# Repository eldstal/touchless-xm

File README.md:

# Touchlæss XM

A mod for Sony WH-1000XM2 (experimental), WH-1000XM3, WH-1000XM4 and WH-1000XM5 (experimental) headphones to remove the gesture-based touch controls and add physical buttons.

- [Project Status](#Status)
- [Compatible headsets](#compatibility)
- [Modifications](#modifications-and-faq)
- [How to program your board](#how-to-program)
- [Notes on ordering PCBs](#fabrication-notes)
- [License](#license)

## Status
The project is feature-complete and the electronics are functional. I'd call it a Beta product, since I'm the only user and still tweaking the design details.

### Case
The design has been 3D-printed and test fit against an XM4 headset. The mic grill looks good but prints awful.
Could be that we need to use a metal mesh inserted during the print.

The buttons have different top surfaces, so you can feel which is which. They've also been relocated to be less likely to be accidentally actuated.

STLs will be available both with and without USB ports, with and without the Æ logo.

### PCB
v0.5c of the board has been manufactured and works great!

I've installed it in my own headset for some day-to-day testing.

### Firmware
Ready to go. USB support (only for programming) is already included in the main board. The project uses platform.io and OptiBoot to run an Arduino-based firmware.

## Compatibility
I only have a pair of XM4 to test with, so the design is made to fit them. The connector is a 24-pin, but only XM5 has a cable that wide. For other models, insert your narrower cable carefully to match the lines on the PCB.

### 🟡 Sony WH-1000XM2 (Experimental)
I've laid out the board for experimental support for the XM2. These are the most different out of the bunch, so there are caveats.

⚠️**WARNING**⚠️
The OEM cable will not work, because the XM2 has the touch board's connector at the front. You will need a slightly longer cable **with opposite side contacts**. Possibly [This Würth 687712100002](https://eu.mouser.com/ProductDetail/Wurth-Elektronik/687712100002?qs=PhR8RmCirEbjmYLiy2w9eg%3D%3D) is suitable, but too long of a cable will cause interference. If you can trim it to length, that will improve the chances of success.

There is no bespoke connector for the XM2, you need to very carefully position it in the larger connector using the lines on the PCB.

It's also necessary to modify the firmware pin map slightly, since the Y pins are in the opposite order. Use `--environment xm2` when you compile the firmware.

If you've got a pair of XM2s and want to help me tune the compatibility, let me know!

### 🟡 Sony WH-1000XM3 (Probably compatible)
The XM3 touch board and battery connector appear to be electrically identical to XM4, so the PCB should be compatible. A different case design may be needed.

Insert your cable all the way at the top of the connector (there will be two unused pins at the bottom). Follow the lines in the silkscreen for guidance.

### 🟢 Sony WH-1000XM4 (Compatible)
The project is designed for these, so these will be the ones primarily tested. The OEM touch board has a flat cable which Touchlæss is designed to reuse.

Insert your cable all the way at the top of the connector (there will be two unused pins at the bottom). Follow the lines in the silkscreen for guidance.

The battery uses a 2-pin JST ZH series connector. There is no vertical space inside the case for a matching connector on the board, so I've resorted to soldering a Y-connector onto the Touchlæss pcb. Separate from the PCB BOM, you'll need one male and one female JST ZH-2 connector and some red/black cables.

### 🟡 Sony WH-1000XM5 (Possibly compatible)
Experimental support is included in the initial board design, but I **do not** own a pair of XM5 and cannot test them. The XM5 pinout is entirely based on reverse-engineering of photos, so I may have made a mistake! The Touchless board shouldn't be able to do any damage to the headphones. If you have a pair of XM5s and would like to help me test the compatibility, feel free to reach out!

At a minimum, the XM5 OEM design doesn't include a loose cable for us to reuse. You will need a suitable flat cable, which is 24-pin FFC with 0.5mm pitch and same-side connectors. [This Würth 687624050002](https://eu.mouser.com/ProductDetail/Wurth-Elektronik/687624050002?qs=P%2FTEqz%252BQfndQFFKLalvVUA%3D%3D) should work, but may not be the proper length.

The battery connector for XM5 is also different, a 3-pin of unknown design. If you have more information about this, let me know!

### 🟡 Sony WH-1000XM6 (Not even released yet)
With any luck, the XM6 touch board will be similar to the XM5. It will be a while before I get my hands on a new high-end headset to test it, though.

If you're getting a pair of XM6 and would like to send me some nice photos of the internals, I'll be very grateful!

### 🔴 Other manufacturers/headsets
**Highly** unlikely. At the very least, you'll need to figure out the pinout for the touch sensor board. Most likely there will be other things that need tuning as well. If you want to make something like touchless for a different headset, take a look at the [technical documentation](doc/README.md) for some pointers on how Touchless works.

## Modifications and FAQ

#### Will it drain my battery?
Not really. When idle, the board draws about 0.02 mA. When you're actively pressing/holding buttons it peaks at just under 13mA. This is on the order of one LED, and only when you're actively pushing buttons.

The DC converter on the board will stop working once the battery drops below about 0.7V, which is quite a bit before the headphones actually stop working. That means the buttons won't work when your battery is very low.

#### I don't want another USB port on my headset
That's OK, it's only needed for development (reprogramming the Touchless board without disassembling the headphones). Simply snap the USB connector off from the main board (see perforations) and print yourself a case without a USB block. Set `cap_type=nousb` in `xm4-cap.scad` to get a case that's closed at the bottom.

#### I don't like how you've placed the buttons
That's no problem! Snap the button portion off of the main board (see perforations) and use the solder points on the front or back to connect your own buttons placed wherever you want them. If you're keen on PCB design, it's not that hard to redesign the PCB for button placement (or add/remove buttons as needed).

There is no need for external resistors etc, just connect a switch between one button contact and the COM and you're good to go.

#### I don't have a 3D printer
No problem! If you remove the buttons and the USB addition (see above), the touchless board should fit inside the OEM ear cup (you have to remove the original touch board first, which may be destructive). Make cuts in the case as needed to mount buttons where you want them, and wire them up to the exposed button solder points on the front or back of the PCB.

#### The case is fine, but I want to reconfigure the buttons
Easiest way to do this is in the firmware. Take a look at [buttonmap.cpp](firmware/tobo/src/buttonmap.cpp) to switch and swap however you like. You'll need the included USB port or a serial cable to program the board after you've made your modifications. Instructions are [down below](#step-2-firmware).

#### Any tips for software modifications?
The board itself works as its own development board, of sorts. If you're going to be flashing new software via USB while testing, I recommend connecting the USB V (+5v) pad to the VCC test point as shown in [this photo](doc/usbpower.png). If you also short out the "LED" solder bridge you get LED indications of which touch points are currently being "touched".

**Please disconnect the USB power jumper before installing in the headset and connecting a battery**

#### I want to design my own case
Great! You can find the dimensions of the PCB [here](doc/tobo-measurements.svg). It's all  relative to the center of the circular area, so if your CAD program supports polar coordinates you'll have an easier time of it. You may also have use for `make vrml` in the pcb directory, which creates a VRML 3D export of the PCB to use as a reference in your model.

#### I want buttons for other features
That won't be possible, sorry. Touchlæss only works by simulating touches and swipes, so it can only do what the headphones allow you to do with the touch panel.

#### The buttons are too slow!
Yes. There is a significant delay between pushing a button and the headset responding. This isn't something we can control, since Touchlæss simulates touch gestures. If a swipe takes 120ms to perform, the headset can't react sooner than that.

#### I want the buttons on the left cup
That will be an adventure. Touchlæss interfaces with the board in the right cup, so you'll need to run wires across the headband to get to the other side. Not impossible, but certainly a lot of work.

#### I want to make and sell these
That's great! I won't ask for any royalties or whatever. If you do set something up, I'm happy to include a link here so people can buy from you.

## How to program

**Note:** The VCC loop on the PCB is powered by the headset battery via a step up/step down converter configured for 3.3V. **Do not** connect an external supply to this hook while the battery is connected. The loop is only needed in order to program and test the board without a headset connected.

The board will not take power from the USB connector by default. If you want to power it via USB while programming, connect a jumper between the USB V test point and the VCC test point as illustrated [here](doc/usbpower.png). Disconnect that jumper again before connecting a battery, please.

### Step 1: Bootloader
**This only needs to be done once per board**

When you have a fresh board with a factory-stock microcontroller, you'll have to start with the bootloader. For this step you need a hardware AVR programmer, for example:

- AVRISPmk2 (tested, works)
- An Arduino ([Instructions](https://docs.arduino.cc/built-in-examples/arduino-isp/ArduinoISP/#how-to-wire-your-boards))
- A [Bus Pirate](http://www.dangerousprototypes.com/docs/Bus_Pirate_AVR_Programming)
- An [USBAsp](https://www.fischl.de/usbasp/)

...or anything else supported by avrdude or [platform.io](https://platformio.org/). Install [the platform.io tools](https://platformio.org/install/cli) and let's go!

1. Connect your programmer to MISO, MOSI, SCK, GND and RST.
2. Connect the battery or the VCC terminal

| tobo | AVRISP 10-pin |Glasgow | BP harness |
|------|---------------|--------|------------|
| MOSI | 1             | PURP   | 8 Pink     |
| VCC  | 2             | ORG    | 2 White    |
| RST  | 5             | YEL    | 6 Green    |
| SCK  | 7             | PINK   | 7 Yellow   |
| MISO | 9             | BRN    | 10 Brown   |
| GND  | 10            | B/W    | 1 Black    |

If you're using a new kind of programmer, add the needed environment to `firmware/tobo/platformio.ini` to use your programmer.

**Warning** Ensure that your new environment extends `env:tobo`, so that the frequency and fuses are programmed properly. If you do not, you may need to temporarily connect an external crystal (see PCB markings) in order to recover the board.

```
cd firmware/tobo
pio run --environment avrispv2 --target bootloader
```

If there are no errors, congratulations! Your tobo board is an Arduino! You're ready for the next step.

### Step 2: Firmware
**If you've made changes to the code and want to update your board, this step is the only one you need to repeat**

If your board has the bootloader installed, you can put your ISP programmer away and use either the on-board USB port or your own serial adapter. This can be an FTDI cable, a different USB-to-serial adapter, or an arduino board with no microcontroller.

Hook up your serial cable to the tobo:

| tobo | serial adapter |
|------|----------------|
| RX | TX |
| TX | RX |
| GND | GND |
| DTR | DTR (if your cable has it) |
| RST | RST (if using an arduino) |
| VCC  | VCC **Only if you don't have the battery plugged in**|

```
cd firmware/tobo
pio run --target upload
```

If all went well, you're ready to go!

## Fabrication Notes
I've had the board produced by PCBWay with no issues. The following facts are useful while setting up an order:

- Order a 0.6mm PCB, to maximize the clearance inside the cap
- The smallest drilled hole is just over 0.2mm
- The XM4/XM5 connector footprints have narrow spacing between pads. This is a problem for the "Matte black" solder mask, but apparently possible with green/blue/red solder mask. If you want a matte black board, you have to allow for gaps in the solder mask at these connectors, and that may lead to shorts. Go with green or blue or red.

## Cost
The total cost for production, components and assembly of 5 boards was about $280 including shipping to Europe and VAT. That works out to about $56 per board.
You can reduce the BOM cost some by removing the USB port, USB-Serial circuitry and the LEDs. You could also save a bit by not populating the test loops, but it will make it more difficult to program the board.

## License
Touchlæss XM © 2026 by Albin Eldstål-Ahrens is licensed under Creative Commons BY-SA 4.0 

This means you are free to use, modify, distribute, remix, redesign the project however you wish as long as you
1. Credit the original work where relevant
2. Release your own modified work under a similar CC license

If you want to make and sell kits of this, feel free! If you make money from my work, please consider making a donation to a charitable organization as a thank you!

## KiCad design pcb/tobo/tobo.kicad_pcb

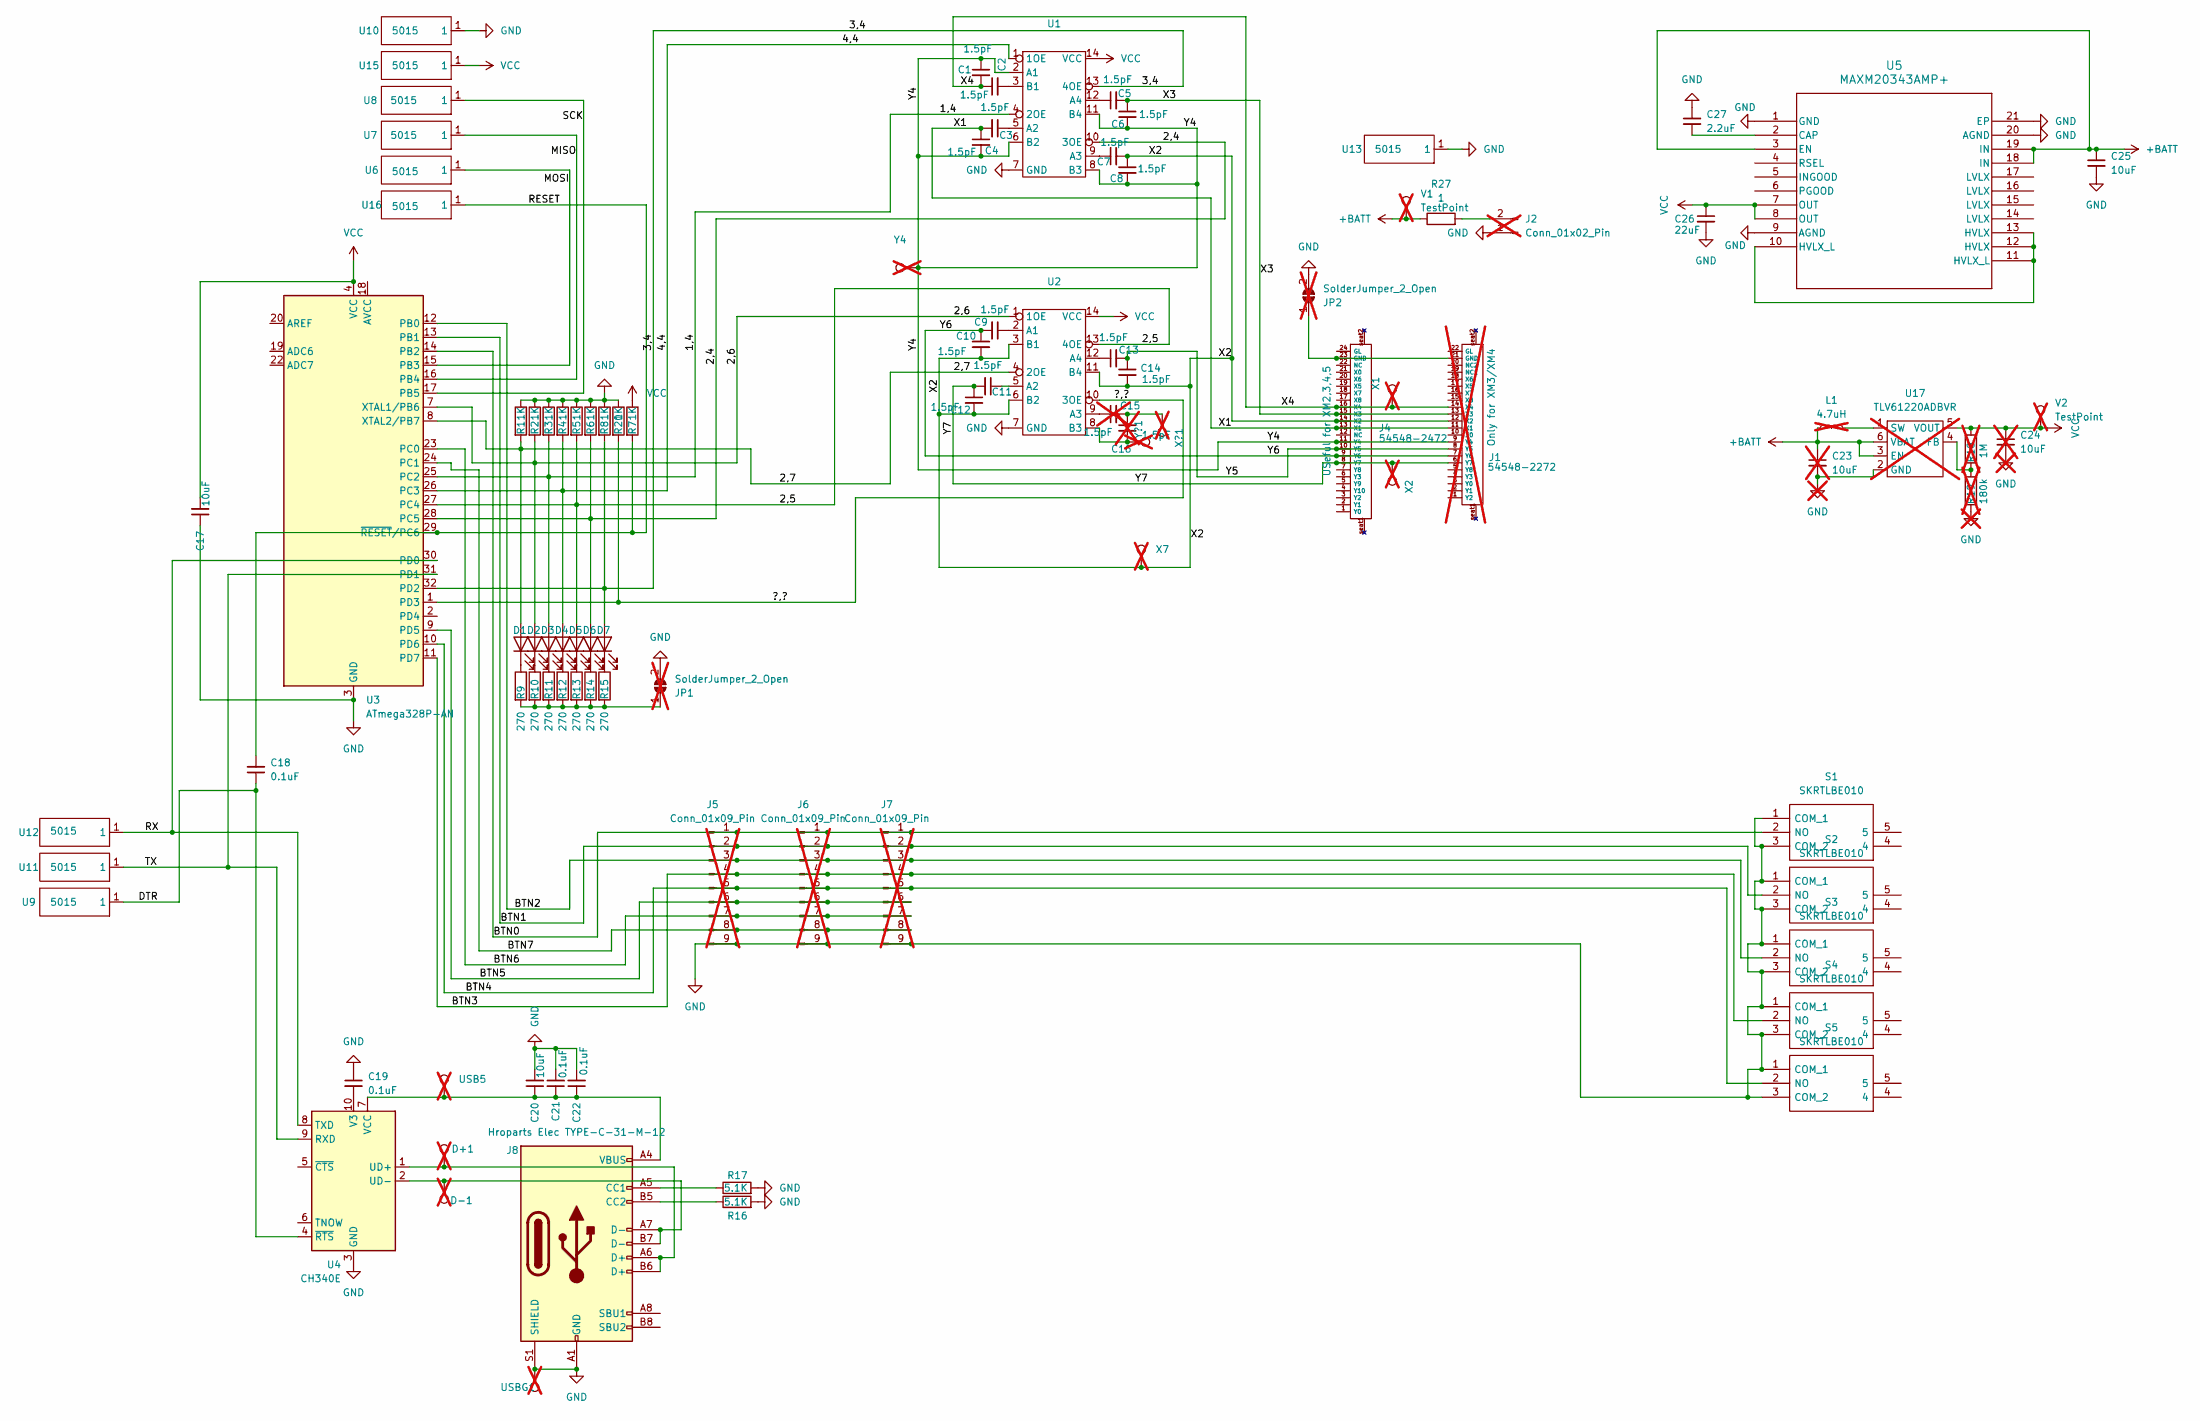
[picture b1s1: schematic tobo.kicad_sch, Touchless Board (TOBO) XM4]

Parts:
C1, C2, C3, C4, C5, C6, C7, C8, C9, C10, C11, C12, C13, C14: 1.5pF; C_0402_1005Metric; Manufacturer_Part_Number CC0402BRNPO9BN1R5; LCSC Part Number C282238
C15, C16: 1.5pF; C_Disc_D5.0mm_W2.5mm_P2.50mm; Manufacturer_Part_Number CC0402BRNPO9BN1R5; LCSC Part Number C282238; not fitted
C17, C20, C25: 10uF; C_0402_1005Metric; Manufacturer_Part_Number CL05A106MP5NUNC; LCSC Part Number C315248
C18, C19, C21, C22: 0.1uF; C_0201_0603Metric; Mouser Part Number 963-TMK063ABJ104KP-F
C23, C24: 10uF; C_0402_1005Metric; Manufacturer_Part_Number CL05A106MP5NUNC; LCSC Part Number C315248; not fitted
C26: 22uF; C_0402_1005Metric; Manufacturer_Part_Number CL05A226MQ5QUNC; LCSC Part Number C105226
C27: 2.2uF; C_0402_1005Metric; Manufacturer_Part_Number CL05A225KO5NQNC; LCSC Part Number C170151
D1, D2, D3, D4, D5, D6, D7: LED; LED_0201_0603Metric; Manufacturer_Part_Number XL-0201UYC; LCSC Part Number C5440628
D+1: TestPoint; TestPoint_Pad_D1.0mm; not fitted
D-1: TestPoint; TestPoint_Pad_D1.0mm; not fitted
J1: 54548-2272; molex-545482272; Mouser Part Number 538-54548-2272; not fitted
J2: Conn_01x02_Pin; power-cable; not fitted
J4: 54548-2472; molex-545482472; Mouser Part Number 538-54548-2472
J5: Conn_01x09_Pin; button_breakout_2.54mm; not fitted
J6, J7: Conn_01x09_Pin; button_breakout_0.5mm; not fitted
J8: Hroparts Elec TYPE-C-31-M-12; USB_C_Receptacle_HRO_TYPE-C-31-M-12; Manufacturer_Part_Number TYPE-C-31-M-12; LCSC Part Number C165948
JP1, JP2: SolderJumper_2_Open; SolderJumper-2_P1.3mm_Open_RoundedPad1.0x1.5mm; not fitted
L1: 4.7uH; L_1008_2520Metric; Mouser Part Number 571-365708M4R7T; not fitted
R1, R2, R3, R4, R5, R6, R7, R8, R20: 1K; R_0201_0603Metric; Mouser Part Number 667-ERJ-1GJJ102C
R9, R10, R11, R12, R13, R14, R15: 270; R_0201_0603Metric; Mouser Part Number 667-ERJ-1GNF2700C
R16, R17: 5.1K; R_0201_0603Metric; Mouser Part Number 667-ERA-1AEC512C
R18: 1M; R_0201_0603Metric; Mouser Part Number 667-ERJ-1GJF1004C; not fitted
R19: 180k; R_0201_0603Metric; Mouser Part Number 667-ERJ-1GJF1803C; not fitted
R27: 1; R_0805_2012Metric; Mouser Part Number 667-ERJ-6DQF1R0V
S1, S2, S3, S4, S5: SKRTLBE010; Mouser Part Number 688-SKRTLB
U1, U2: VSSOP50P400X100-14N; Mouser Part Number 757-TC7MBL3125CFKEL
U3: ATmega328P-AN; TQFP-32_7x7mm_P0.8mm; Mouser Part Number 556-ATMEGA328P-AN
U4: CH340E; MSOP-10_3x3mm_P0.5mm_narrowpads; Manufacturer_Part_Number CH340E; LCSC Part Number C99652
U5: MAXM20343AMP+; 21-100447_ADI; Manufacturer_Part_Number MAXM20343AMP+; Mouser Part Number 700-MAXM20343AMP+
U6, U7, U8, U9, U10, U11, U12, U13, U15, U16: 5015; Manufacturer_Part_Number 5015; Mouser Part Number 534-5015
U17: TLV61220ADBVR; SOT-23-6; Mouser Part Number 595-TLV61220ADBVR; not fitted
USB5: TestPoint; TestPoint_Pad_D1.0mm; not fitted
USBG1: TestPoint; TestPoint_Pad_D1.0mm; not fitted
V1, V2: TestPoint; TestPoint_Pad_D1.0mm; not fitted
X1, X2, X7: TestPoint; TestPoint_Pad_D1.0mm; not fitted
X?1: TestPoint; TestPoint_Pad_D1.0mm; not fitted
Y4: TestPoint; TestPoint_Pad_D1.0mm; not fitted
Y?1: TestPoint; TestPoint_Pad_D1.0mm; not fitted

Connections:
+BATT: C23.1, C25.1, L1.1, R27.1, U5.3 (EN), U5.18 (IN), U5.19 (IN), U17.3 (EN), U17.6 (VBAT), V1.1
/1,4: D3.2 (A), R3.2, U1.4 (2OE), U3.25 (PC2)
/2,4: D6.2 (A), R6.2, U1.10 (3OE), U3.28 (PC5)
/2,5: D5.2 (A), R5.2, U2.13 (4OE), U3.27 (PC4)
/2,6: D2.2 (A), R2.2, U2.1 (1OE), U3.7 (XTAL1/PB6)
/2,7: D1.2 (A), R1.2, U2.4 (2OE), U3.8 (XTAL2/PB7)
/3,4: D7.2 (A), R8.2, U1.13 (4OE), U3.32 (PD2)
/4,4: D4.2 (A), R4.2, U1.1 (1OE), U3.26 (PC3)
/?,?: R20.2, U2.10 (3OE), U3.1 (PD3)
/BTN0: J5.1, J6.1, J7.1, S1.2 (NO), U3.14 (PB2)
/BTN1: J5.2, J6.2, J7.2, S2.2 (NO), U3.13 (PB1)
/BTN2: J5.3, J6.3, J7.3, S3.2 (NO), U3.12 (PB0)
/BTN3: J5.4, J6.4, J7.4, S4.2 (NO), U3.11 (PD7)
/BTN4: J5.5, J6.5, J7.5, S5.2 (NO), U3.10 (PD6)
/BTN5: J5.6, J6.6, J7.6, U3.9 (PD5)
/BTN6: J5.7, J6.7, J7.7, U3.23 (PC0)
/BTN7: J5.8, J6.8, J7.8, U3.24 (PC1)
/DTR: C18.1, U4.4 (~RTS), U9.1
/MISO: U3.16 (PB4), U7.1
/MOSI: U3.15 (PB3), U6.1
/RESET: C18.2, R7.2, U3.29 (~RESET/PC6), U16.1
/RX: U3.30 (PD0), U4.8 (TXD), U12.1
/SCK: U3.17 (PB5), U8.1
/TX: U3.31 (PD1), U4.9 (RXD), U11.1
/X1: C3.2, C4.1, J1.11 (X1), J4.13 (X1)
/X2: C7.2, C8.1, C10.2, C12.2, C14.2, J1.12 (X2), J4.14 (X2), U2.3 (B1), U2.6 (B2), U2.11 (B4), X7.1
/X3: C5.2, C6.1, J1.13 (X3), J4.15 (X3)
/X4: C1.2, C2.1, J1.14 (X4), J4.16 (X4), X1.1
/Y4: C1.1, C4.2, C6.2, C8.2, J1.9 (Y4), J4.11 (Y4), U1.2 (A1), U1.6 (B2), U1.8 (B3), U1.11 (B4), Y4.1
/Y5: C13.2, C14.1, J1.8 (Y5), J4.10 (Y5)
/Y6: C9.2, C10.1, J1.7 (Y6), J4.9 (Y6)
/Y7: C11.2, C12.1, J1.6 (Y7), J4.8 (Y7), X2.1
GND: C17.1, C19.1, C20.2, C21.2, C22.2, C23.2, C24.2, C25.2, C26.2, C27.1, J2.1, J5.9, J6.9, J7.9, J8.A1 (GND), J8.A12 (GND), J8.B1 (GND), J8.B12 (GND), J8.S1 (SHIELD), JP1.2 (B), JP2.2 (B), R1.1, R2.1, R3.1, R4.1, R5.1, R6.1, R8.1, R16.2, R17.2, R19.2, R20.1, S1.1 (COM_1), S1.3 (COM_2), S2.1 (COM_1), S2.3 (COM_2), S3.1 (COM_1), S3.3 (COM_2), S4.1 (COM_1), S4.3 (COM_2), S5.1 (COM_1), S5.3 (COM_2), U1.7 (GND), U2.7 (GND), U3.3 (GND), U3.5 (GND), U3.21 (GND), U4.3 (GND), U5.1 (GND), U5.9 (AGND), U5.20 (AGND), U5.21 (EP), U10.1, U13.1, U17.2 (GND), USBG1.1
unnamed: C15.2, C16.1, X?1.1
unnamed: D1.1 (K), R9.1
unnamed: D2.1 (K), R10.1
unnamed: D3.1 (K), R11.1
unnamed: D4.1 (K), R12.1
unnamed: D5.1 (K), R13.1
unnamed: D6.1 (K), R14.1
unnamed: D7.1 (K), R15.1
unnamed: J2.2, R27.2
unnamed: J1.21 (GND), J4.23 (GND), JP2.1 (A)
unnamed: J8.A5 (CC1), R17.1
unnamed: J8.B5 (CC2), R16.1
unnamed: JP1.1 (A), R9.2, R10.2, R11.2, R12.2, R13.2, R14.2, R15.2
unnamed: L1.2, U17.1 (SW)
unnamed: R18.2, R19.1, U17.4 (FB)
unnamed: C3.1, U1.5 (A2)
unnamed: C7.1, U1.9 (A3)
unnamed: C5.1, U1.12 (A4)
unnamed: C2.2, U1.3 (B1)
unnamed: C9.1, U2.2 (A1)
unnamed: C11.1, U2.5 (A2)
unnamed: C15.1, U2.9 (A3)
unnamed: C13.1, U2.12 (A4)
unnamed: C16.2, U2.8 (B3), Y?1.1
unnamed: D+1.1, J8.A6 (D+), J8.B6 (D+), U4.1 (UD+)
unnamed: D-1.1, J8.A7 (D-), J8.B7 (D-), U4.2 (UD-)
unnamed: C19.2, U4.10 (V3)
unnamed: C20.1, C21.1, C22.1, J8.A4 (VBUS), J8.A9 (VBUS), J8.B4 (VBUS), J8.B9 (VBUS), U4.7 (VCC), USB5.1
unnamed: C27.2, U5.2 (CAP)
unnamed: U5.10 (HVLX_L), U5.11 (HVLX_L), U5.12 (HVLX), U5.13 (HVLX)
VCC: C17.2, C24.1, C26.1, R7.1, R18.1, U1.14 (VCC), U2.14 (VCC), U3.4 (VCC), U3.6 (VCC), U5.7 (OUT), U5.8 (OUT), U15.1, U17.5 (VOUT), V2.1

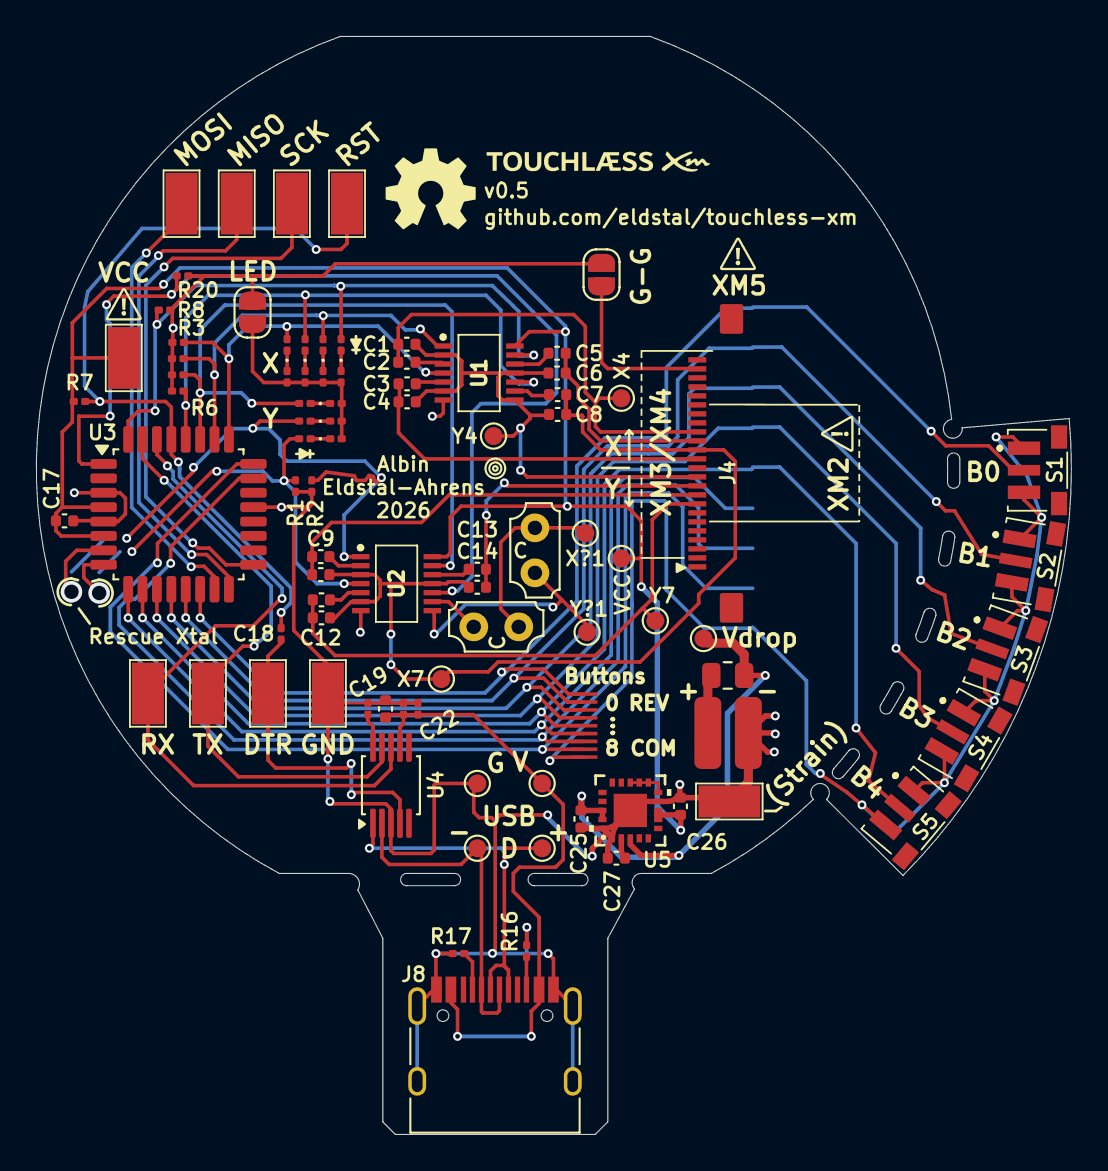
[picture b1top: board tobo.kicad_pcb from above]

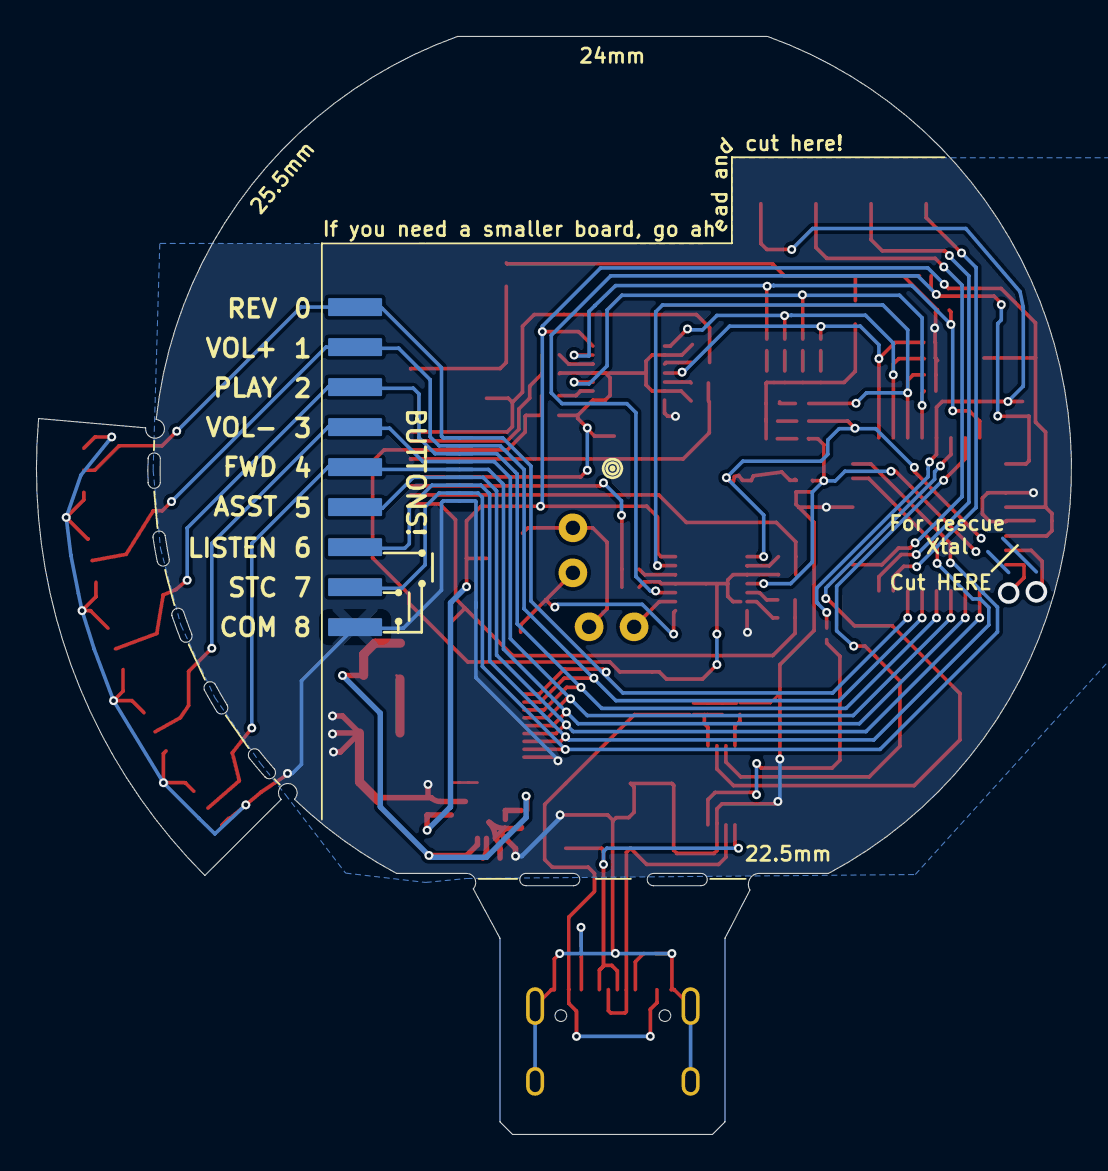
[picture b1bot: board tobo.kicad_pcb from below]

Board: 2 copper layers, 57.5 x 61.0 mm, 91 parts (2 on the bottom side), 62 nets.

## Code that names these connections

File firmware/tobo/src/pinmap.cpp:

#include "pinmap.hpp"
#include "headsets.hpp"

const unsigned char BTN_PIN[N_BTNS] = {
    PIN_PB2,
    PIN_PB1,
    PIN_PB0,
    PIN_PD7,
    PIN_PD6,
    PIN_PD5,
    PIN_PC0,
    PIN_PC1
};

const unsigned char BTN_INT[N_BTNS] {
    2,  // PB2
    1,  // PB1
    0,  // PB0
    23, // PD7
    22, // PD6
    21, // PD5
    7,  // PB7
    6   // PB6
};



// Touch points across different X values
const unsigned char TOUCH_X_PIN[N_TOUCH_X] {
    PIN_PC2,  // 1,4   rear
    PIN_PC5,  // 2,4
    PIN_PD2,  // 3,4
    PIN_PC3,  // 4,4   front
};


// Touch points across different Y values
#ifdef IS_XM2
    // The XM2 has its Y pins in a different order
    // in the cable, so we correct for that here
    const unsigned char TOUCH_Y_PIN[N_TOUCH_Y] {
        PIN_PB7, // 2,0,  bottom
        PIN_PB6, // 2,1
        PIN_PC4, // 2,2
        PIN_PC5  // 2,3,  top
    };

#else
    const unsigned char TOUCH_Y_PIN[N_TOUCH_Y] {
        PIN_PC5,  // 2,4,  bottom
        PIN_PC4,  // 2,5
        PIN_PB6,  // 2,6
        PIN_PB7,  // 2,7,  top
    };
#endif

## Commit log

2025-04-29 Design is untested, ready for first prototype run.
2025-04-29 A readme
2025-04-29 License text
2025-04-29 Connector models
2025-04-29 Another 3d render fix
2025-04-30 More documentation and a more permissive license
2025-04-30 License changes and more docs
2025-05-01 Cleanup
2025-05-01 Normalize PCB trace thickness and add a VCC attachment
2025-05-03 A first little platform.io project to burn the bootloader and firmware
2025-05-03 Don't forget how to do this
2025-05-04 Tweaks
2025-05-04 A pinmap, maybe
2025-05-04 A more compatible bootloader (lower baud rate) seems more stable.
2025-05-04 PCB tweaks
2025-05-04 Fixed DRC violation
2025-05-04 Made the PCB prettier
2025-05-04 PCB cleanup, RST connector clarification
2025-05-04 More documentation
2025-05-04 Separate DTR from RST pin. They are different.
2025-05-04 Fix URL in logo
2025-05-04 DRC fix
2025-05-04 Connector name fix
2025-05-05 Minor little wip
2025-05-05 An idea for how to implement dynamic gestures, maybe
2025-05-05 A working gesture!
2025-05-06 Cleared edges of USB board
2025-05-06 Interrupts!
2025-05-06 Fix messed up indentation
2025-05-06 Internal pull-ups for the buttons. May as well.
2025-05-06 Firmware button handlers and debouncing
2025-05-06 Untented all the vias in order to allow a crystal
    We don't actually need one, but if you mess up burning
    the bootloader, you may need to hold a crystal to the contacts
    in order to correct the programming.
    In Kicad 9, we may be able to re-tent all the vias and untent these.
    That would be nice.
2025-05-07 Confirmed pinouts of XM5 and XM5.
    Experimental support for XM2 added.
2025-05-07 Phrasing
2025-05-08 PCB and documentation tweaks
2025-05-08 Missing optiboot URL
2025-05-08 Can't just turn the board around for XM2, actually.
2025-05-08 Simplified bootloader/fuses setup. Platformio does it for us!
2025-05-08 Swapped some GPIO to avoid PCINT problems
    This lead to a tasty basket weave of traces under the MCU, but that's
    fine I guess.
    The only reason this change was "necessary" is because regular arduino
    doesn't expose gpio on the crystal pins. Therefore the PCINT libraries
    don't seem to support enabling the pin change interrupt on those pins.
    It was neat to have them as buttons, from a routing perspective, but
2025-05-10 Maybe we can use TPU filament raw for a gasket?
2025-05-10 Three-point swipes are enough, it seems
2025-05-10 Endless PCB tweaks
2025-05-10 OpenSCAD build configurations
2025-05-10 An attempt at automation of OpenSCAD export
2025-05-10 Naming
2025-05-10 A makefile to generate STLs
2025-05-10 Broke the buttons out of the SCAD exports
2025-05-13 Fixed order of Y LEDs
2025-05-13 Silkscreen guide for hand soldering to a different headset
2025-05-14 Options for faster OpenSCAD export
2025-05-14 Remove the endcaps on the button box.
    I'd like to include the buttons in the case design better, but not sure
    just how.
    I guess the only -important- shapes are the cutouts for PCB and buttons,
    the casing itself can be any wonky shape...
2025-05-15 Fitting of XM4 cap. Screw holes etc are good!
2025-05-15 More fit tweaking. Untested.
2025-05-16 Separate the mic grill from the rest of the print
2025-05-17 Part numbers selected
2025-05-17 Moved autogenerated PCB files to dist/
2025-05-17 Auto-generate gerber files
2025-05-17 BOM export
2025-05-17 Drill file format
2025-05-18 Minor tweaks before first PCB order
2025-05-18 Robustered locator pegs
2025-05-18 Some notes on PCB ordering
2025-05-18 Bumped PCB version to v1.0a
    Changes will still be made, I just want it to be labeled
    differently from the ones I've ordered for fabrication
2025-05-19 Attempts to clear up some printing problems.
    There's still a section of weak wall just above the button box, for some
    reason. Prusa slicer makes it a single wall rather than the solid
    double-layer it uses around the rest of the perimeter.
2025-05-19 Screw posts properly aligned for XM4
2025-05-19 Made the board significantly cheaper to manufacture.
    Now there's only one connector (these things are like $5 each :D)
    and some of the caps were super expensive too.
    Also fixed some incomplete part numbers, so the BOM should be
    better for the next attempt at fabrication.
2025-05-19 Documentation of the new single-connector design
2025-05-19 Fixed an ugly wall breach in the cap model
2025-05-19 New PCB render for the single-connector design
2025-05-20 Oops, the connector was on the "safe to cut" board.
    It's not a functional issue, just don't go nuts with the saw!
2025-05-20 Explain yourself in the schematic
2025-05-20 Fixed printing inconsistency in the PCB mounting surface
2025-05-20 Update README.md
    I'm not asking for donations, I'm asking you to donate elsewhere.
2025-05-20 Model names corrected
2025-05-20 "Release" v0.3a of the PCB, ready for manufacture.
    BOM cost is about $17 per board.
2025-05-20 CAD drawing of 0.3a board
2025-05-20 Automatic CAD preview generation
2025-05-20 A dummy PCB to 3d-print for fit testing
2025-05-21 Clearance trimming for PCB mount
2025-05-21 Embiggened buttons, tried to make mic hole print cleanly
2025-05-21 Adaptations for printing (cut down overhangs, etc.
    In particular, the buttons are now more suited to printing without
    support, face up. Sad about the surface, which became really nice when
    printed face down.
2025-05-21 Print-friendly buttons. We'll see.
2025-05-21 Better USB board mounting.
    Also eliminated some more overhangs. We're getting there.
2025-05-22 Button tweaks
2025-05-22 Cleaned up parameters in SCAD
2025-05-22 Documentation update
2025-05-23 Updated previews
2025-05-23 Re-added missing xm4-preview model and fixed previews again
2025-05-23 Cleaned up configs a bit. Added a cool button cutaway.
2025-05-23 Fixed parts rendering
2025-05-23 Built-in print supports for the two tricky openings
2025-05-23 Another attempt at a microphone grill
2025-05-26 Screenshot updates
2025-05-27 Extraneous comment
2025-05-29 Added clarification to silkscreen
    Also bumped PCB version to 0.4
2025-05-30 Adjusted PCB clips and print supports
2025-06-02 Clean up release directory
2025-06-02 PCB measurement documentation
2025-06-02 OK, a little readability tweak
2025-06-03 Better image placement in README
2025-06-12 Programmer connection clarification
2025-06-17 Progress!
2025-06-17 Managed to get the bootloader programmed with buspirate
    Still can't upload the main firmware, though...
2025-06-17 First errata. Yay.
2025-06-18 Solution to the PCB error in v0.3a
    If you've got a v0.4 board, no need to futz around with RX/TX.
2025-06-18 Images in errata documentation
2025-12-25 PCB: Bump to Kicad 9 and preparation for step-up transformer
2025-12-25 First stab at a step-up converter on the tobo
2025-12-28 Half-way to a better transformer
2025-12-28 A mostly one-chip up- and down- converter.
    This should work down to 0.5V, which is just a little bit over the low
    battery warning of the headset.
2025-12-28 Minor versioning shenanigans
2025-12-28 Some kind of bug in screenshot generation
    Nothing should have changed in the SCAD files, but I have no idea why
    openscad regenerated them or why git diffs them as changed
2025-12-28 Sync commit
2025-12-29 Reworked PCB to use TC7MBL3125CFK bus switches
    The old design didn't work, and I suspect it's due to the excessive
    capacitance of the analog mux. This chip (~roughly) has been tested
    against XM4s on the bench and works great with 1.5pF capacitors.
2025-12-29 New screenshots
2025-12-29 Inverted mux control signals for v0.5 board
2026-01-03 Unused controller now has through-hole caps for experimentation
2026-01-04 PCB tweaks and prettification
2026-01-04 PCB tweaks and screenshot prettier
2026-01-07 Added missing pull-up for previously unused control channel
2026-01-09 OK, last little change before next prototype goes off for manufacturing
2026-01-09 Hooked the voltage converter up the right way around. Good catch!
2026-01-13 Finalized files for PCB v0.5, which have been accepted by the fab house
2026-02-10 Reduced brown-out voltage (new board wasn't working at 3.3!)
2026-02-10 Fixed incorrect Bus Pirate harness colors
2026-02-10 Great news!
2026-02-10 A more cheerful summary
2026-02-11 Production notes
2026-02-11 A note about power consumption
2026-02-14 Preparations for a case with a logo medallion on it
2026-02-14 An attempt to better differentiate the buttons
2026-02-14 A big fat logo on the outside, maybe?
2026-02-14 Less gaudy logo rendering
2026-02-15 New approach to the microphone grill
2026-02-15 Flattened xm4-parts model, so everyting prints on one surface
2026-02-18 Shortened buttons slightly
2026-02-18 Make ZIP files for all the case variations
2026-02-18 Case body tweaks
2026-02-18 Thicker cap body, hopefully reduces distortion of outside
2026-02-20 Printability fixes and tweaks to PCB mount
2026-02-23 Preparations for a slightly pulled-in button layout
    In the previous design, laying the headset on a table would press the
    top button.
    This redesign pulls it in 2mm so that the headset rests on the frame
    instead. It requires some more tweaking of the button box, though.
2026-02-23 Slight adjustment of mic hole location
2026-02-26 Move button box out of the way of the headset's table stance
    We'll see if it interferes with the fork. The USB flavor looks pretty
    bad now, since this required rotating the PCB but that's fine.
